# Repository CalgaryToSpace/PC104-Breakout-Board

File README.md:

# PC104-Breakout-Board
A quick PCB to break out the PC104 connector for flatsat testing

## PCB

## Resources

* PC104 Dimensional Specification: https://dspace.cvut.cz/bitstream/handle/10467/94475/F3-BP-2021-Geib-Filip-bp_GEIB.pdf
    * Figure 2.2 (Page 11): Technical dimensional drawing
    * Appendix C (Page 65): PC104 Connector Pinout
        * Note: This is somewhat of a recommendation; every mission selects their own pinout.

## License

CERN Open Hardware Licence Version 2 - Permissive

Feel free to use as you see fit!

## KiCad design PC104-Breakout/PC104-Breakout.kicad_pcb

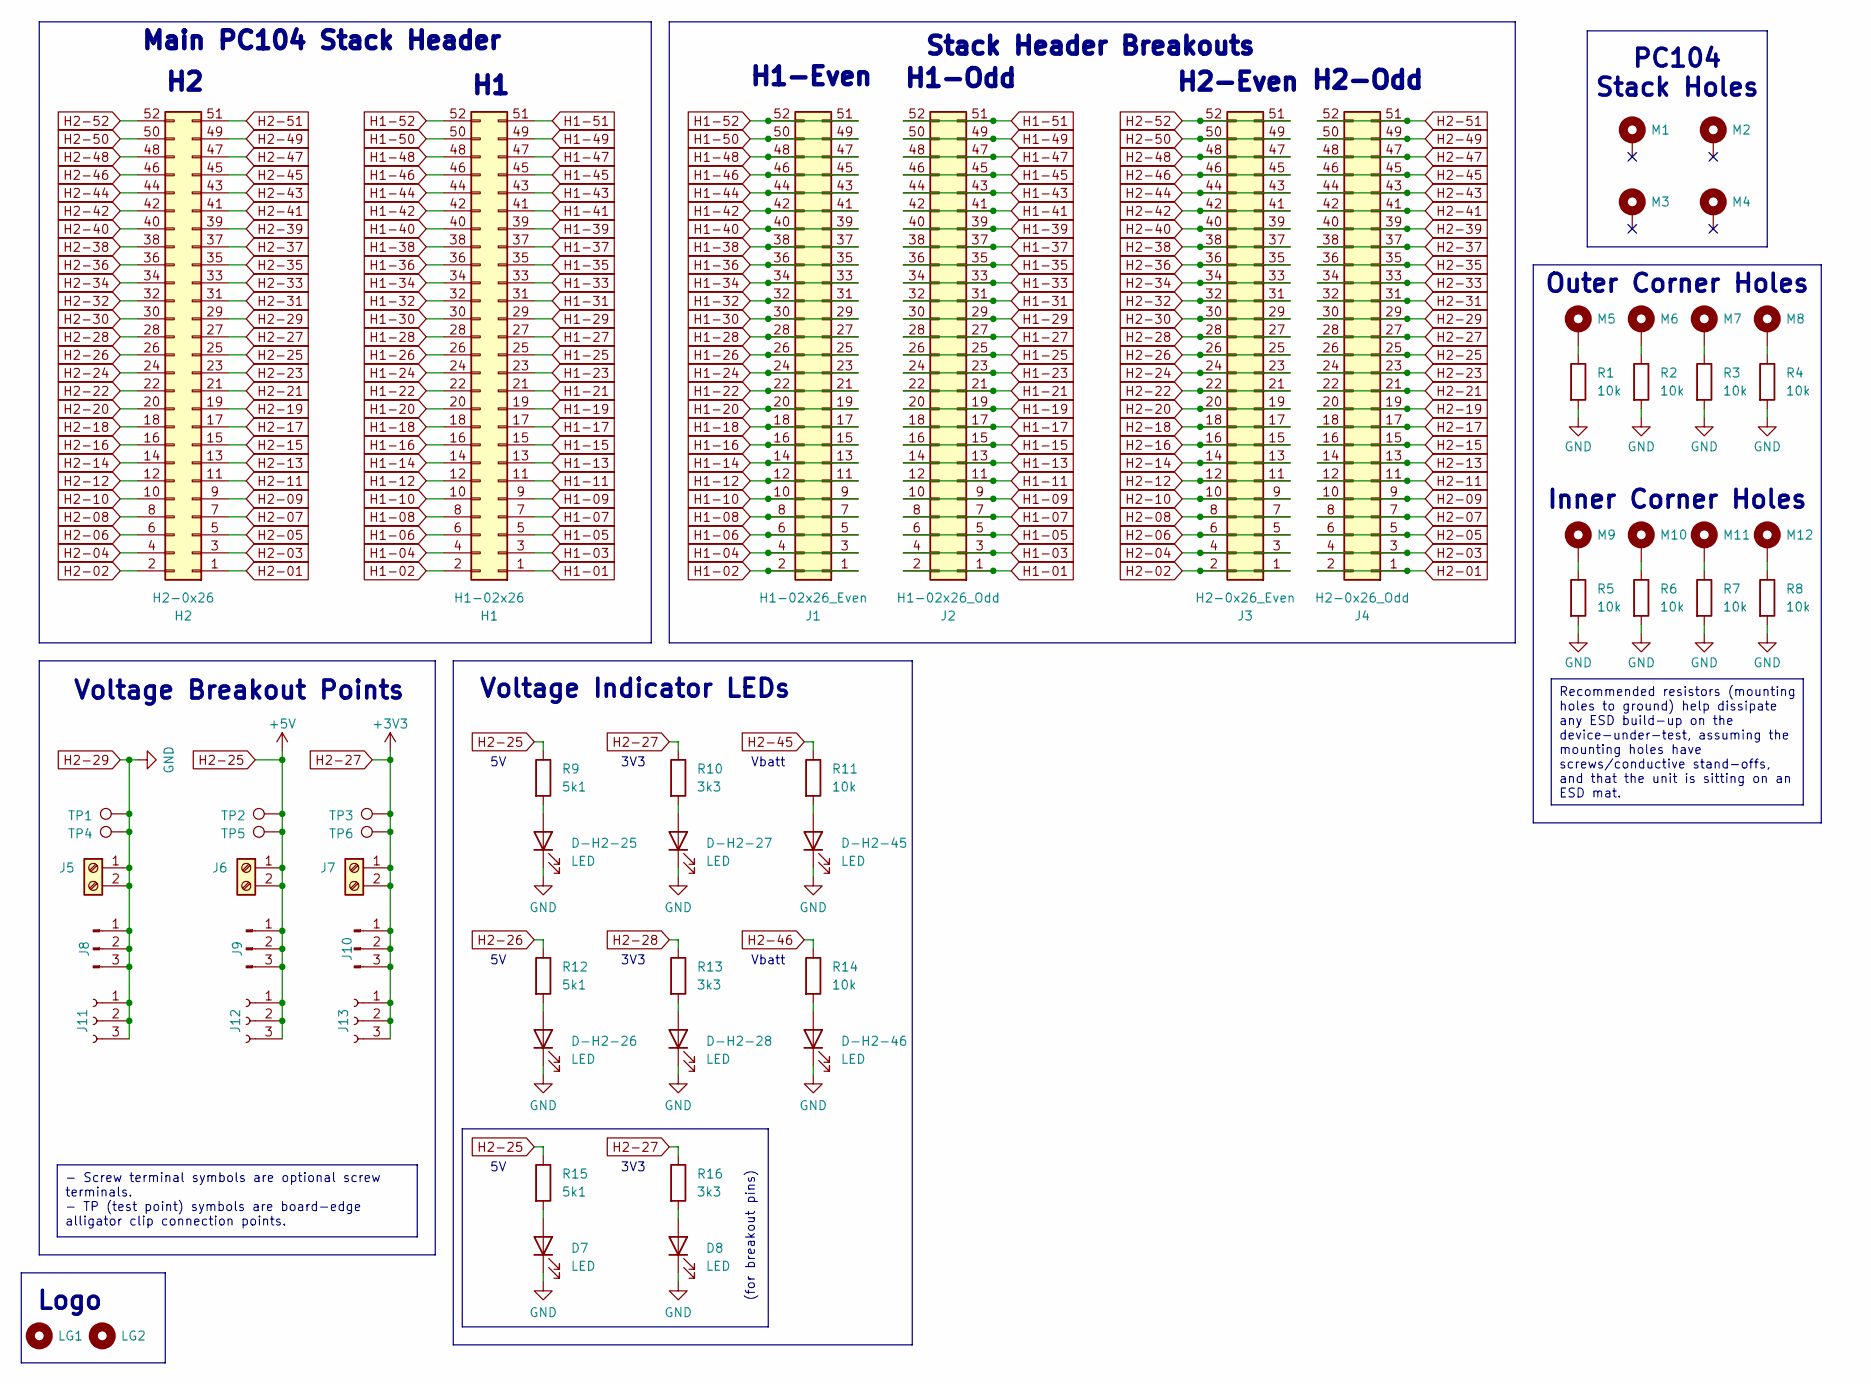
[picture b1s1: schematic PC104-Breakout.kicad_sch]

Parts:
D7, D8: LED; LED_0603_1608Metric_Pad1.05x0.95mm_HandSolder
D-H2-25, D-H2-26, D-H2-27, D-H2-28, D-H2-45, D-H2-46: LED; LED_0603_1608Metric_Pad1.05x0.95mm_HandSolder
H1: H1-02x26; PinSocket_2x26_P2.54mm_Vertical_TightPlacement
H2: H2-0x26; PinSocket_2x26_P2.54mm_Vertical_TightPlacement
J1: H1-02x26_Even; PinHeader_2x26_P2.54mm_Vertical_HeaderAndSocket
J2: H1-02x26_Odd; PinHeader_2x26_P2.54mm_Vertical_HeaderAndSocket
J3: H2-0x26_Even; PinHeader_2x26_P2.54mm_Vertical_HeaderAndSocket
J4: H2-0x26_Odd; PinHeader_2x26_P2.54mm_Vertical_HeaderAndSocket
J5, J6, J7: Screw_Terminal_01x02; TerminalBlock_bornier-2_P5.08mm
J8, J9, J10: Conn_01x02; PinHeader_1x03_P2.54mm_Vertical
J11, J12, J13: Conn_01x03_Socket; PinSocket_1x03_P2.54mm_Vertical
LG1, LG2: MountingHole; CTS-Logo-50x25
M1, M2, M3, M4, M5, M6, M7, M8, M9, M10, M11, M12: MountingHole_Pad; MountingHole_3.2mm_M3_Pad
R1, R2, R3, R4, R5, R6, R7, R8, R11, R14: 10k; R_0603_1608Metric_Pad0.98x0.95mm_HandSolder
R9, R12, R15: 5k1; R_0603_1608Metric_Pad0.98x0.95mm_HandSolder
R10, R13, R16: 3k3; R_0603_1608Metric_Pad0.98x0.95mm_HandSolder
TP1, TP2, TP3, TP4, TP5, TP6: TestPoint; EdgeAlligatorConnector

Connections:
H1-01: H1.1, J2.1, J2.2
H1-02: H1.2, J1.1, J1.2
H1-03: H1.3, J2.3, J2.4
H1-04: H1.4, J1.3, J1.4
H1-05: H1.5, J2.5, J2.6
H1-06: H1.6, J1.5, J1.6
H1-07: H1.7, J2.7, J2.8
H1-08: H1.8, J1.7, J1.8
H1-09: H1.9, J2.9, J2.10
H1-10: H1.10, J1.9, J1.10
H1-11: H1.11, J2.11, J2.12
H1-12: H1.12, J1.11, J1.12
H1-13: H1.13, J2.13, J2.14
H1-14: H1.14, J1.13, J1.14
H1-15: H1.15, J2.15, J2.16
H1-16: H1.16, J1.15, J1.16
H1-17: H1.17, J2.17, J2.18
H1-18: H1.18, J1.17, J1.18
H1-19: H1.19, J2.19, J2.20
H1-20: H1.20, J1.19, J1.20
H1-21: H1.21, J2.21, J2.22
H1-22: H1.22, J1.21, J1.22
H1-23: H1.23, J2.23, J2.24
H1-24: H1.24, J1.23, J1.24
H1-25: H1.25, J2.25, J2.26
H1-26: H1.26, J1.25, J1.26
H1-27: H1.27, J2.27, J2.28
H1-28: H1.28, J1.27, J1.28
H1-29: H1.29, J2.29, J2.30
H1-30: H1.30, J1.29, J1.30
H1-31: H1.31, J2.31, J2.32
H1-32: H1.32, J1.31, J1.32
H1-33: H1.33, J2.33, J2.34
H1-34: H1.34, J1.33, J1.34
H1-35: H1.35, J2.35, J2.36
H1-36: H1.36, J1.35, J1.36
H1-37: H1.37, J2.37, J2.38
H1-38: H1.38, J1.37, J1.38
H1-39: H1.39, J2.39, J2.40
H1-40: H1.40, J1.39, J1.40
H1-41: H1.41, J2.41, J2.42
H1-42: H1.42, J1.41, J1.42
H1-43: H1.43, J2.43, J2.44
H1-44: H1.44, J1.43, J1.44
H1-45: H1.45, J2.45, J2.46
H1-46: H1.46, J1.45, J1.46
H1-47: H1.47, J2.47, J2.48
H1-48: H1.48, J1.47, J1.48
H1-49: H1.49, J2.49, J2.50
H1-50: H1.50, J1.49, J1.50
H1-51: H1.51, J2.51, J2.52
H1-52: H1.52, J1.51, J1.52
H2-01: H2.1, J4.1, J4.2
H2-02: H2.2, J3.1, J3.2
H2-03: H2.3, J4.3, J4.4
H2-04: H2.4, J3.3, J3.4
H2-05: H2.5, J4.5, J4.6
H2-06: H2.6, J3.5, J3.6
H2-07: H2.7, J4.7, J4.8
H2-08: H2.8, J3.7, J3.8
H2-09: H2.9, J4.9, J4.10
H2-10: H2.10, J3.9, J3.10
H2-11: H2.11, J4.11, J4.12
H2-12: H2.12, J3.11, J3.12
H2-13: H2.13, J4.13, J4.14
H2-14: H2.14, J3.13, J3.14
H2-15: H2.15, J4.15, J4.16
H2-16: H2.16, J3.15, J3.16
H2-17: H2.17, J4.17, J4.18
H2-18: H2.18, J3.17, J3.18
H2-19: H2.19, J4.19, J4.20
H2-20: H2.20, J3.19, J3.20
H2-21: H2.21, J4.21, J4.22
H2-22: H2.22, J3.21, J3.22
H2-23: H2.23, J4.23, J4.24
H2-24: H2.24, J3.23, J3.24
H2-25: H2.25, J4.25, J4.26, J6.1, J6.2, J9.1, J9.2, J9.3, J12.1, J12.2, J12.3, R9.1, R15.1, TP2.1, TP5.1
H2-26: H2.26, J3.25, J3.26, R12.1
H2-27: H2.27, J4.27, J4.28, J7.1, J7.2, J10.1, J10.2, J10.3, J13.1, J13.2, J13.3, R10.1, R16.1, TP3.1, TP6.1
H2-28: H2.28, J3.27, J3.28, R13.1
H2-29: D7.1 (K), D8.1 (K), D-H2-25.1 (K), D-H2-26.1 (K), D-H2-27.1 (K), D-H2-28.1 (K), D-H2-45.1 (K), D-H2-46.1 (K), H2.29, J4.29, J4.30, J5.1, J5.2, J8.1, J8.2, J8.3, J11.1, J11.2, J11.3, R1.2, R2.2, R3.2, R4.2, R5.2, R6.2, R7.2, R8.2, TP1.1, TP4.1
H2-30: H2.30, J3.29, J3.30
H2-31: H2.31, J4.31, J4.32
H2-32: H2.32, J3.31, J3.32
H2-33: H2.33, J4.33, J4.34
H2-34: H2.34, J3.33, J3.34
H2-35: H2.35, J4.35, J4.36
H2-36: H2.36, J3.35, J3.36
H2-37: H2.37, J4.37, J4.38
H2-38: H2.38, J3.37, J3.38
H2-39: H2.39, J4.39, J4.40
H2-40: H2.40, J3.39, J3.40
H2-41: H2.41, J4.41, J4.42
H2-42: H2.42, J3.41, J3.42
H2-43: H2.43, J4.43, J4.44
H2-44: H2.44, J3.43, J3.44
H2-45: H2.45, J4.45, J4.46, R11.1
H2-46: H2.46, J3.45, J3.46, R14.1
H2-47: H2.47, J4.47, J4.48
H2-48: H2.48, J3.47, J3.48
H2-49: H2.49, J4.49, J4.50
H2-50: H2.50, J3.49, J3.50
H2-51: H2.51, J4.51, J4.52
H2-52: H2.52, J3.51, J3.52
unnamed: D7.2 (A), R15.2
unnamed: D8.2 (A), R16.2
unnamed: D-H2-25.2 (A), R9.2
unnamed: D-H2-26.2 (A), R12.2
unnamed: D-H2-27.2 (A), R10.2
unnamed: D-H2-28.2 (A), R13.2
unnamed: D-H2-45.2 (A), R11.2
unnamed: D-H2-46.2 (A), R14.2
unnamed: M5.1, R1.1
unnamed: M6.1, R2.1
unnamed: M7.1, R3.1
unnamed: M8.1, R4.1
unnamed: M9.1, R5.1
unnamed: M10.1, R6.1
unnamed: M11.1, R7.1
unnamed: M12.1, R8.1

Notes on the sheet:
- Screw terminal symbols are optional screw terminals. - TP (test point) symbols are board-edge alligator clip connection points.
Recommended resistors (mounting holes to ground) help dissipate any ESD build-up on the device-under-test, assuming the mounting holes have screws/conductive stand-offs, and that the unit is sitting on an ESD mat.
(for breakout pins)
Outer Corner Holes
Vbatt
H2-Odd
Voltage Indicator LEDs
Inner Corner Holes
PC104 Stack Holes
Stack Header Breakouts
Logo
3V3
Voltage Breakout Points
Main PC104 Stack Header
H1-Odd
H1-Even
H2-Even

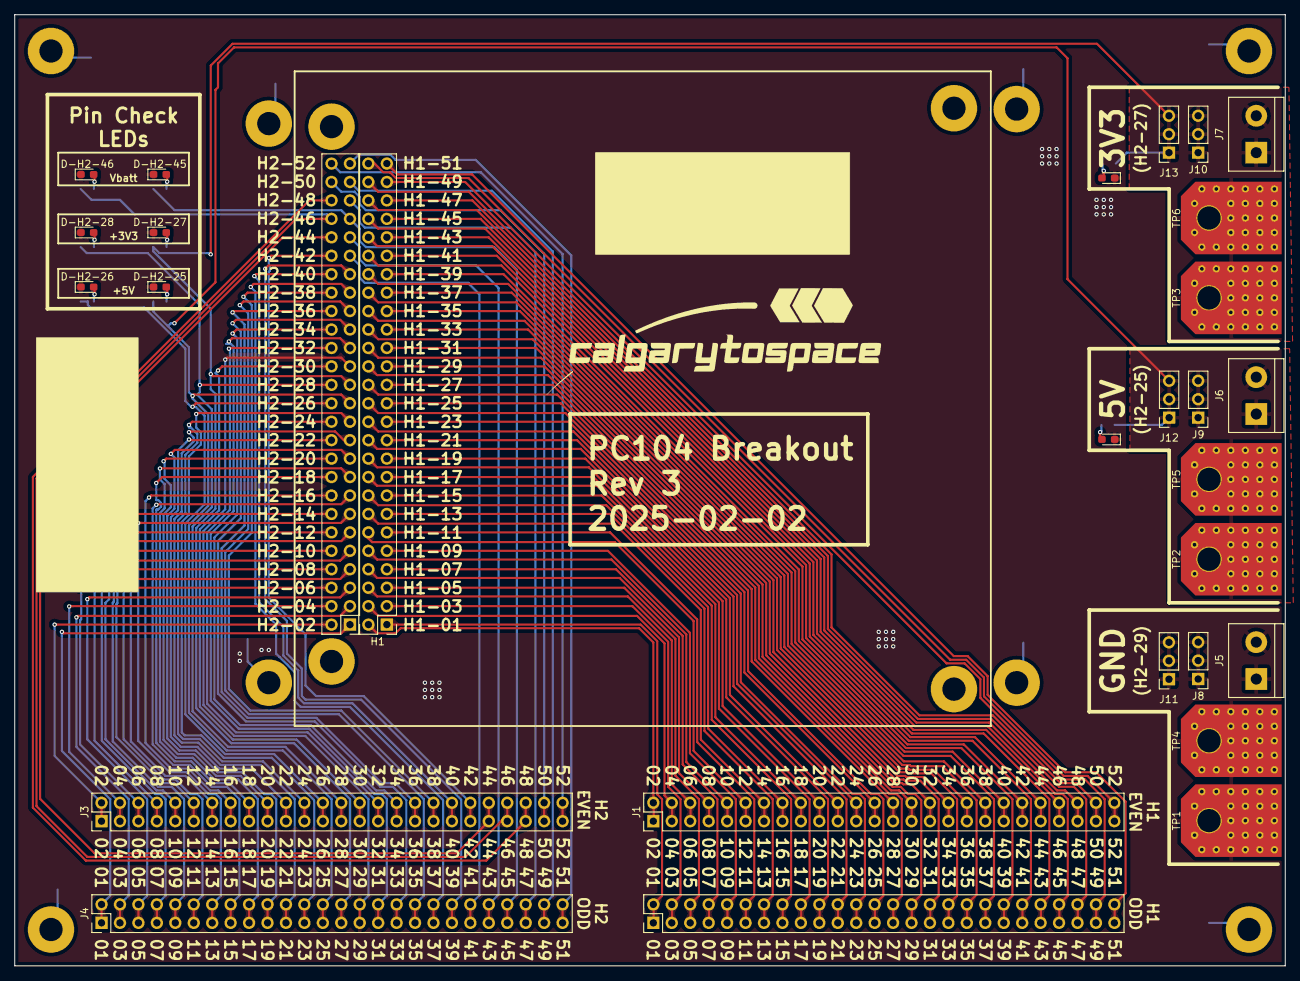
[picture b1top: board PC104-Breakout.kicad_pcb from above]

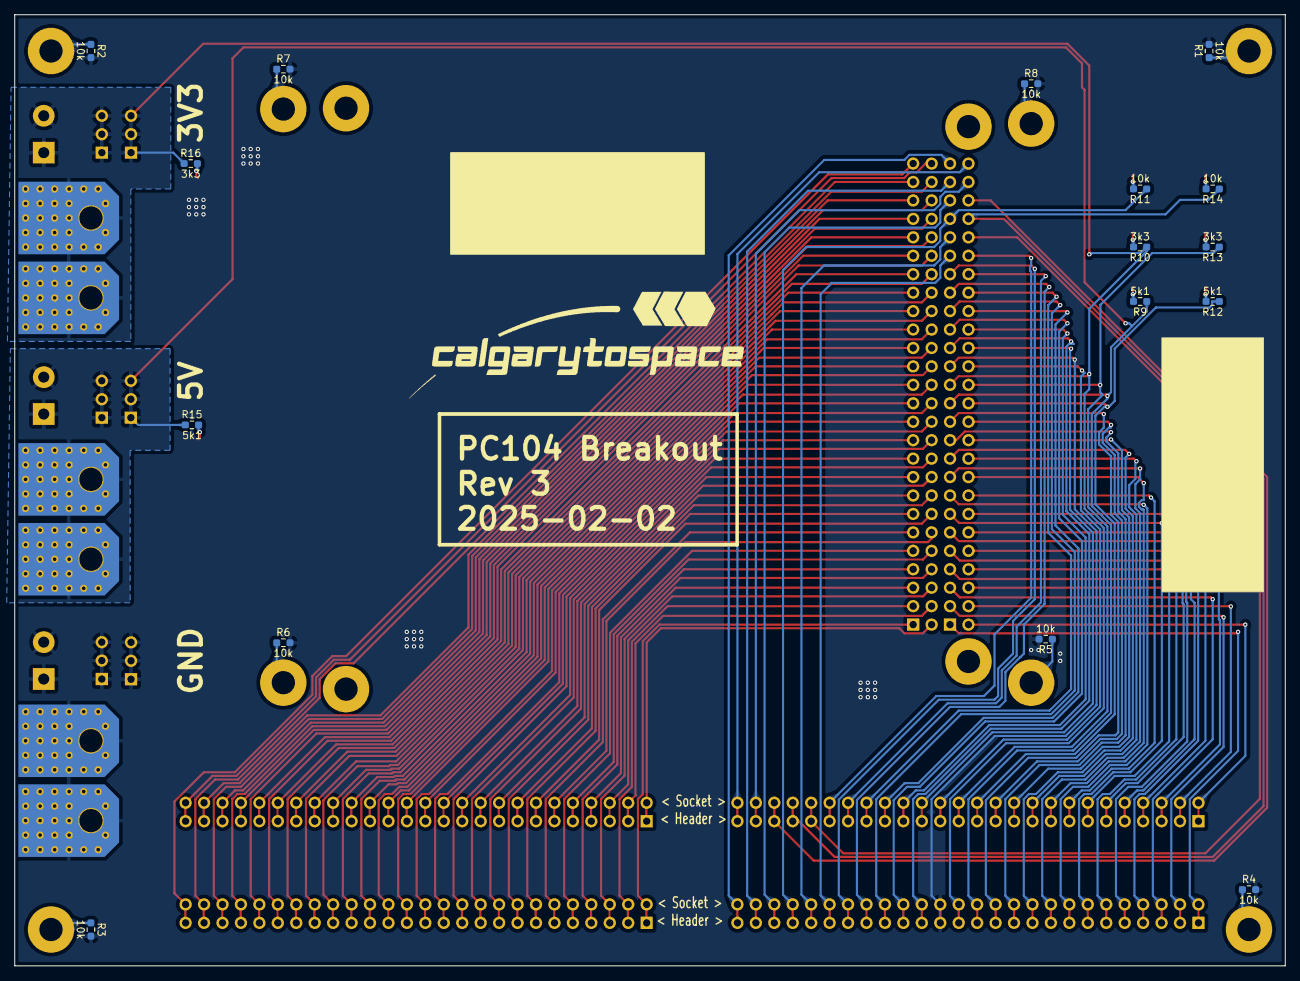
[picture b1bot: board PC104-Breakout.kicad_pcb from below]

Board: 2 copper layers, 175.0 x 131.0 mm, 59 parts (17 on the bottom side), 120 nets.

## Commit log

2024-04-27 Add license, update README
2024-04-27 created schematic
    - H1 and H2
    - GND, 5V, 3V3 connectors
2024-04-27 flipped headers to face correct direction
2024-04-27 updated pcb file
    updated from schematic
2024-05-11 added screwholes
2024-05-14 added silk screens for header pins
2024-05-18 Positioned external mounting holes
2024-05-18 Intense layout/positioning of the PC104 spec
2024-05-18 Added 3.3V and GND LEDs
2024-05-18 semi final routing
    - routed everything including power pins
    - created GND, 3V3, and 5V pours
    - added vias for diodes / routing
    TODO: fix last two unrouted nets
2024-05-18 finished routing
    - fixed final unrouted nets and vias
    - silk screen edits
2024-05-18 Fixed LED orientations and finalized board design
2024-05-21 Added silkscreen - created production files
2024-05-22 Reorganized PCB layout
    Modified layout files to change board from 4 layers to 2 in order to decrease production costs by $45. Shifted two stack headers to the right of the space allocated for the EPS and rerouted with 2 la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
2024-05-22 Completed layout, updated silkscreen and added aesthetic fixes
2024-05-22 Created production files
2024-05-29 Made changes
2025-02-02 Update for Rev 3, do layout
2025-02-02 Polish 3d models, silkscreen
2025-02-02 Polish silkscreen more
2025-02-02 Route H1 breakout
2025-02-02 Reroute H1 with breakout flipped
2025-02-02 Route both H1 and H2
2025-02-02 Finish Rev 3
2025-02-02 Fix DRC issues - Rev 3 final
